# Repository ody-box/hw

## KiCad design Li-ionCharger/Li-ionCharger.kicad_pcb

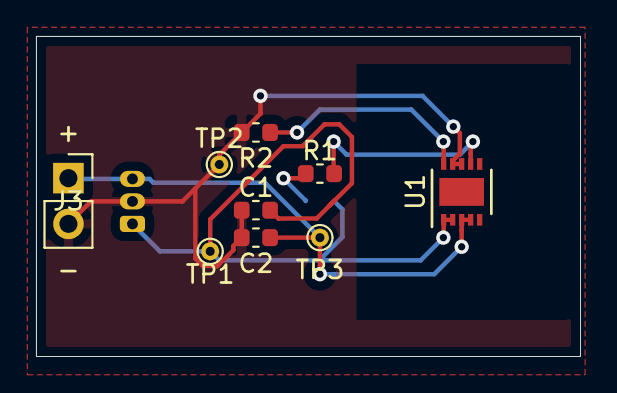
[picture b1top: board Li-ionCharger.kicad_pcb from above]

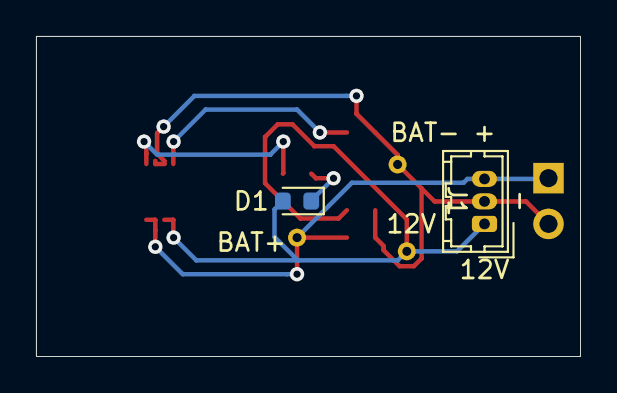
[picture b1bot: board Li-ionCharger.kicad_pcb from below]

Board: 2 copper layers, 30.2 x 17.8 mm, 11 parts (2 on the bottom side), 6 nets.

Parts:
C1, C2: 1uF; C_0603_1608Metric
D1: Blue; LED_0603_1608Metric
J1: Conn_01x03_Male; Hirose_DF13-03P-1.25DSA_1x03_P1.25mm_Vertical
J3: Conn_01x02_Male; PinSocket_1x02_P2.54mm_Vertical
R1: 1k; R_0603_1608Metric
R2: 1.1k 1% E96; R_0603_1608Metric
TP1, TP2, TP3: TestPoint; TestPoint_THTPad_D1.0mm_Drill0.5mm
U1: MCP73213; DFN-10-1EP_3x3mm_P0.5mm_EP1.55x2.48mm

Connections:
12V: C1.1, D1.2, J1.1, TP1.1, U1.1, U1.2
BAT+: C2.1, J1.3, J3.1, TP3.1, U1.3, U1.4
BAT-: C1.2, C2.2, J1.2, J3.2, R2.2, TP2.1, U1.8, U1.9
unnamed: D1.1, R1.2
unnamed: R1.1, U1.7
unnamed: R2.1, U1.10

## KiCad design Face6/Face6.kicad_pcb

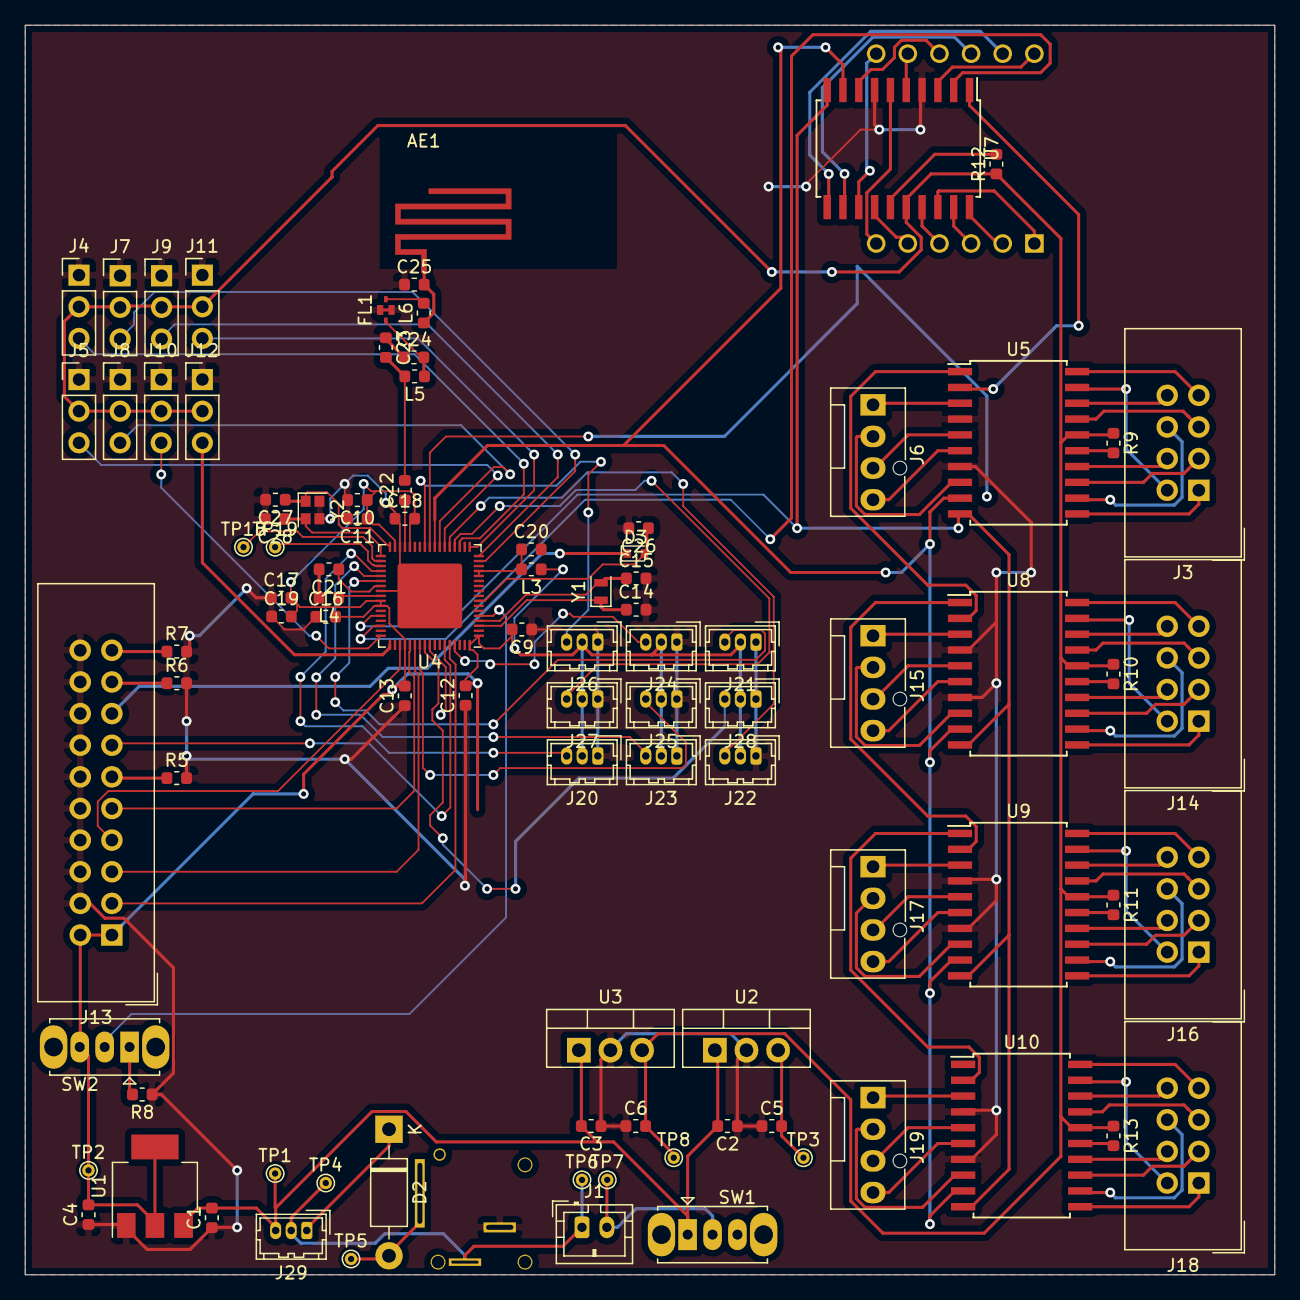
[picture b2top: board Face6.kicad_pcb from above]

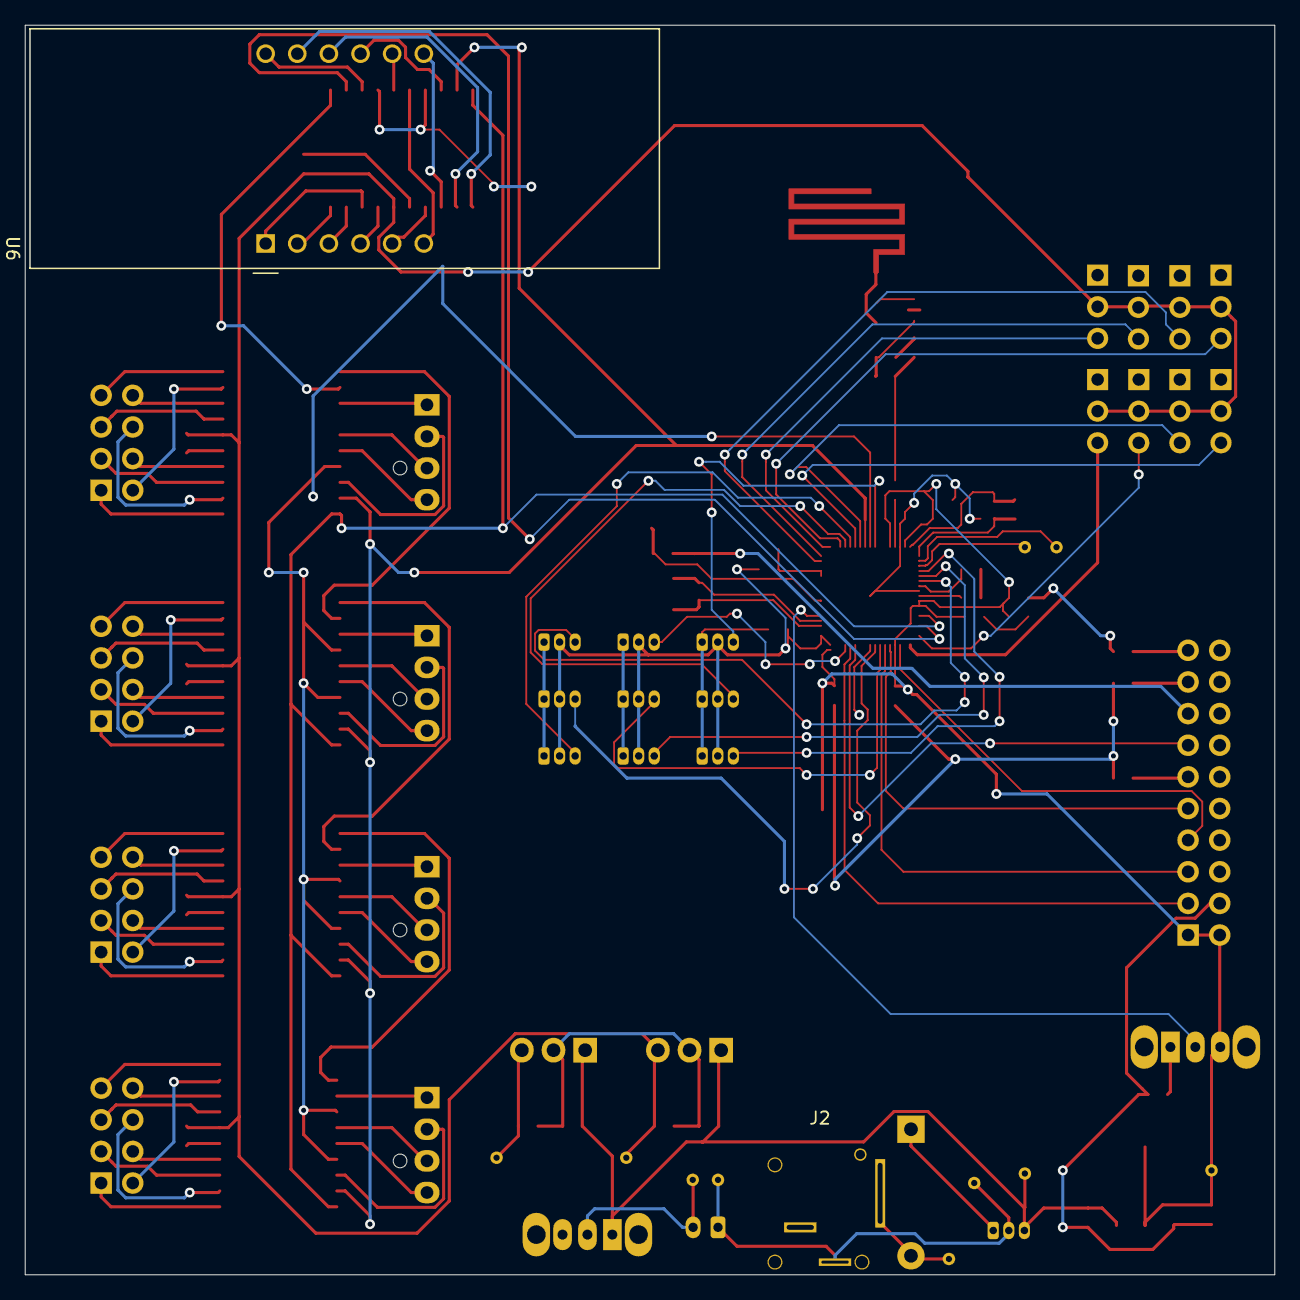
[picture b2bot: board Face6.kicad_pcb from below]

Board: 2 copper layers, 100.3 x 100.3 mm, 96 parts (2 on the bottom side), 125 nets.

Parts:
AE1: Antenna; STM32-Antenna
C1, C5, C6: 0.1uF; C_0603_1608Metric
C2, C3: 0.33uF; C_0603_1608Metric
C4: 10uF; C_0603_1608Metric
C9, C10, C12, C13, C16, C18, C19, C20, C26: 100nF; C_0603_1608Metric
C11: 100pF; C_0603_1608Metric
C14, C15: 10pF; C_0603_1608Metric
C17, C21: 4.7uF; C_0603_1608Metric
C22: 10nF; C_0603_1608Metric
C23: 0.8pF; C_0603_1608Metric
C24: 0.3pF; C_0603_1608Metric
C25: 1.2pF; C_0603_1608Metric
C27, C28: 20pF; C_0603_1608Metric
D2: 1N4007; D_DO-41_SOD81_P10.16mm_Horizontal
D3: BAT54K; D_SOD-523
FL1: DEA162450BT
J1: Conn_01x02_Female; JST_PH_B2B-PH-K_1x02_P2.00mm_Vertical
J2: Barrel_Jack_Switch; KLDVX2020A
J3, J14, J16, J18: Conn_02x04_Odd_Even; IDC-Header_2x04_P2.54mm_Vertical
J4, J5, J7, J8, J9, J10, J11, J12: Conn_01x03_Male; PinHeader_1x03_P2.54mm_Vertical
J6, J15, J17, J19: Conn_01x04; FanPinHeader_1x04_P2.54mm_Vertical
J13: Conn_02x10_Odd_Even; IDC-Header_2x10_P2.54mm_Vertical
J20, J21, J22, J23, J24, J25, J26, J27, J28, J29: Conn_01x03_Male; Hirose_DF13-03P-1.25DSA_1x03_P1.25mm_Vertical
L3: KMZ1608; L_0603_1608Metric
L4: 10uH; L_0603_1608Metric
L5: 2.7nH; L_0603_1608Metric
L6: 3.6nH; R_0603_1608Metric
R5, R6, R7, R8: 10k; R_0603_1608Metric
R9, R10, R11, R13: 22.6k; R_0603_1608Metric
R12: 28k; R_0603_1608Metric
SW1, SW2: SW_SPDT; SW_Slide_1P2T_CK_OS102011MS2Q
TP1, TP2, TP3, TP4, TP5, TP6, TP7, TP8, TP18, TP19: TestPoint; TestPoint_THTPad_D1.0mm_Drill0.5mm
U1: LD1117S33TR_SOT223; SOT-223-3_TabPin2
U2, U3: L7805; TO-220-3_Vertical
U4: STM32WB55REV; QFN-68-1EP_8x8mm_P0.4mm_EP5.2x5.2mm
U5, U7, U8, U9, U10: AS1105WL-T; SOIC-20W_7.5x12.8mm_P1.27mm
U6: CA56-12EWA
Y1: NX2012_32K768; Crystal_SMD_2012-2Pin_2.0x1.2mm
Y2: NX3225SA-32MHz; Crystal_SMD_2016-4Pin_2.0x1.6mm

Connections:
+3V3: C4.2, C9.2, C10.1, C11.1, C12.2, C13.2, C16.2, C17.2, C18.2, C19.2, J13.1, J13.2, J20.2, J21.2, J22.2, J23.2, J24.2, J25.2, J26.2, J27.2, J28.2, L3.1, SW2.3, TP2.1, U1.2, U4.1, U4.30, U4.33, U4.44, U4.45, U4.55, U4.68
+5V: C6.2, J4.2, J5.2, J7.2, J8.2, J9.2, J10.2, J11.2, J12.2, R9.1, R10.1, R11.1, R12.1, R13.1, TP8.1, U3.3, U5.16, U7.16, U8.16, U9.16, U10.16
+5VP: C5.2, TP3.1, U2.3
/Connectors.sch/12V: D2.1, J29.1
/Connectors.sch/BAT+: C1.2, C2.2, C3.2, J29.3, SW1.1, TP1.1, U1.3, U2.1, U3.1
/Connectors.sch/BAT-: J1.1, J2.2, J29.2, TP4.1, TP6.1
/Connectors.sch/DIG0_0: J6.1, U5.3
/Connectors.sch/DIG0_1: J15.1, U8.3
/Connectors.sch/DIG0_2: J17.1, U9.3
/Connectors.sch/DIG0_3: J19.1, U10.3
/Connectors.sch/DIG1_0: J6.2, U5.8
/Connectors.sch/DIG1_1: J15.2, U8.8
/Connectors.sch/DIG1_2: J17.2, U9.8
/Connectors.sch/DIG1_3: J19.2, U10.8
/Connectors.sch/DIG2_0: J6.3, U5.5
/Connectors.sch/DIG2_1: J15.3, U8.5
/Connectors.sch/DIG2_2: J17.3, U9.5
/Connectors.sch/DIG2_3: J19.3, U10.5
/Connectors.sch/DIG3_0: J6.4, U5.6
/Connectors.sch/DIG3_1: J15.4, U8.6
/Connectors.sch/DIG3_2: J17.4, U9.6
/Connectors.sch/DIG3_3: J19.4, U10.6
/Connectors.sch/SEGA_0: J3.1, U5.11
/Connectors.sch/SEGA_1: J14.1, U8.11
/Connectors.sch/SEGA_2: J16.1, U9.11
/Connectors.sch/SEGA_3: J18.1, U10.11
/Connectors.sch/SEGB_0: J3.3, U5.13
/Connectors.sch/SEGB_1: J14.3, U8.13
/Connectors.sch/SEGB_2: J16.3, U9.13
/Connectors.sch/SEGB_3: J18.3, U10.13
/Connectors.sch/SEGC_0: J3.5, U5.17
/Connectors.sch/SEGC_1: J14.5, U8.17
/Connectors.sch/SEGC_2: J16.5, U9.17
/Connectors.sch/SEGC_3: J18.5, U10.17
/Connectors.sch/SEGD_0: J3.7, U5.20
/Connectors.sch/SEGD_1: J14.7, U8.20
/Connectors.sch/SEGD_2: J16.7, U9.20
/Connectors.sch/SEGD_3: J18.7, U10.20
/Connectors.sch/SEGE_0: J3.8, U5.18
/Connectors.sch/SEGE_1: J14.8, U8.18
/Connectors.sch/SEGE_2: J16.8, U9.18
/Connectors.sch/SEGE_3: J18.8, U10.18
/Connectors.sch/SEGF_0: J3.6, U5.12
/Connectors.sch/SEGF_1: J14.6, U8.12
/Connectors.sch/SEGF_2: J16.6, U9.12
/Connectors.sch/SEGF_3: J18.6, U10.12
/Connectors.sch/SEGG_0: J3.4, U5.14
/Connectors.sch/SEGG_1: J14.4, U8.14
/Connectors.sch/SEGG_2: J16.4, U9.14
/Connectors.sch/SEGG_3: J18.4, U10.14
/STM32/GPIO0_2: U4.25, U5.9, U7.9, U8.9, U9.9, U10.9
/STM32/GPIO_EXT0: J20.3, U4.38
/STM32/GPIO_EXT1: J23.3, U4.39
/STM32/GPIO_EXT2: J26.3, U4.27
/STM32/GPIO_EXT4: J21.3, U4.40
/STM32/GPIO_EXT5: J24.3, U4.65
/STM32/GPIO_EXT6: J27.3, U4.21
/STM32/GPIO_EXT7: J22.3, U4.22
/STM32/GPIO_EXT10: J25.3, U4.58
/STM32/GPIO_EXT11: J28.3, U4.59
/STM32/MOSI: U4.49, U7.2
/STM32/PWM1_TM1: J5.3, U4.23
/STM32/PWM1_TM2: J4.3, U4.20
/STM32/PWM2_TM1: J8.3, U4.24
/STM32/PWM2_TM2: J7.3, U4.16
/STM32/PWM3_TM1: J10.3, U4.51
/STM32/PWM3_TM2: J9.3, U4.17
/STM32/PWM4_TM1: J12.3, U4.52
/STM32/PWM4_TM2: J11.3, U4.18
/STM32/SCK: U4.47, U5.10, U7.10, U8.10, U9.10, U10.10
/Sensors/SEGDP_0: J3.2, U5.19
/Sensors/SEGDP_1: J14.2, U8.19
/Sensors/SEGDP_2: J16.2, U9.19
/Sensors/SEGDP_3: J18.2, U10.19
DIG0: U6.12, U7.3
DIG1: U6.9, U7.8
DIG2: U6.8, U7.5
DIG3: U6.6, U7.6
GND: C1.1, C2.1, C3.1, C4.1, C5.1, C6.1, C9.1, C10.2, C11.2, C12.1, C13.1, C14.2, C15.2, C16.1, C17.1, C18.1, C19.1, C20.2, C23.1, C24.1, C25.1, C26.2, C27.2, C28.2, FL1.2, FL1.4, J2.3, J4.1, J5.1, J7.1, J8.1, J9.1, J10.1, J11.1, J12.1, J13.4, J13.6, J13.8, J13.10, J13.12, J13.14, J13.16, J13.18, J13.20, J20.1, J21.1, J22.1, J23.1, J24.1, J25.1, J26.1, J27.1, J28.1, R5.2, R6.2, R7.2, R8.1, U1.1, U2.2, U3.2, U4.32, U4.42, U4.69, U5.4, U5.7, U7.4, U7.7, U8.4, U8.7, U9.4, U9.7, U10.4, U10.7, Y2.3, Y2.4
JTCK: J13.9, U4.56
JTDI: J13.5, U4.57
JTDO: J13.13, U4.63
JTMS: J13.7, U4.54
unnamed: AE1.1, C25.2, L6.1
unnamed: C14.1, U4.3, Y1.1
unnamed: C15.1, U4.4, Y1.2
unnamed: C20.1, L3.2, U4.13, U4.14
unnamed: C21.1, U4.41
unnamed: C21.2, L4.2
unnamed: C22.1, U4.31
unnamed: C22.2, C23.2, L5.2
unnamed: C24.2, FL1.1, L5.1
unnamed: C26.1, D3.2, U4.8
unnamed: C27.1, U4.34, Y2.1
unnamed: C28.1, U4.35, Y2.2
unnamed: D2.2, J2.1, TP5.1
unnamed: FL1.3, L6.2
unnamed: J1.2, SW1.2, TP7.1
unnamed: J13.11, R5.1
unnamed: J13.17, R6.1
unnamed: J13.19, R7.1
unnamed: L4.1, U4.43
unnamed: R8.2, SW2.1
unnamed: R9.2, U5.15
unnamed: R10.2, U8.15
unnamed: R11.2, U9.15
unnamed: R12.2, U7.15
unnamed: R13.2, U10.15
unnamed: SW2.2, U4.5
unnamed: TP18.1, U4.36
unnamed: TP19.1, U4.37
unnamed: U5.1, U8.2
unnamed: U5.2, U7.1
unnamed: U8.1, U9.2
unnamed: U9.1, U10.2
SEGA: U6.11, U7.11
SEGB: U6.7, U7.13
SEGC: U6.4, U7.17
SEGD: U6.2, U7.20
SEGDP: U6.3, U7.19
SEGE: U6.1, U7.18
SEGF: U6.10, U7.12
SEGG: U6.5, U7.14
nJTRST: J13.3, U4.64
nSRST: D3.1, J13.15

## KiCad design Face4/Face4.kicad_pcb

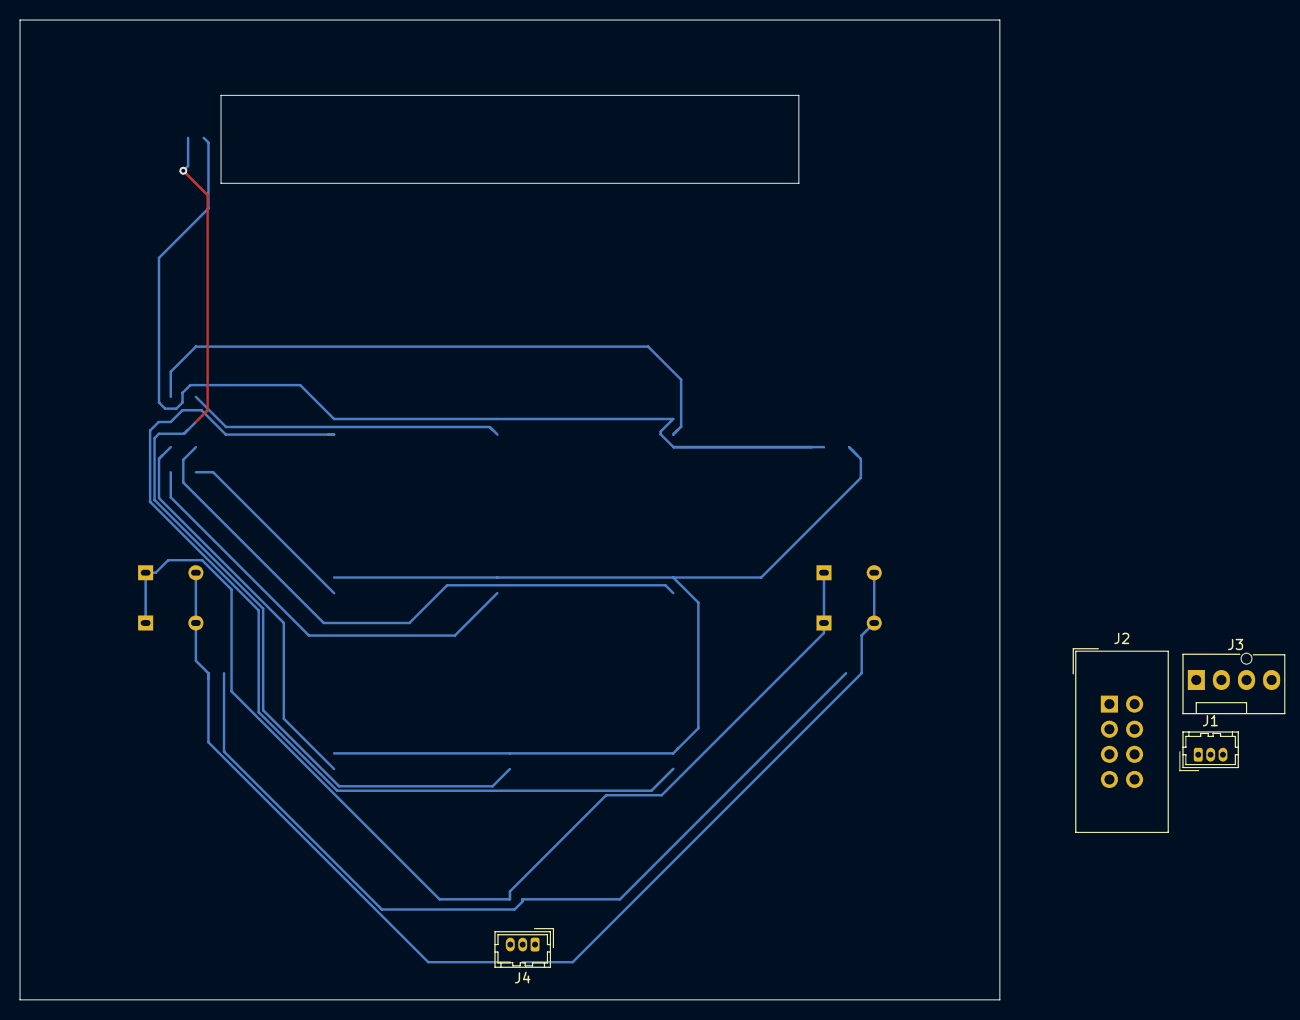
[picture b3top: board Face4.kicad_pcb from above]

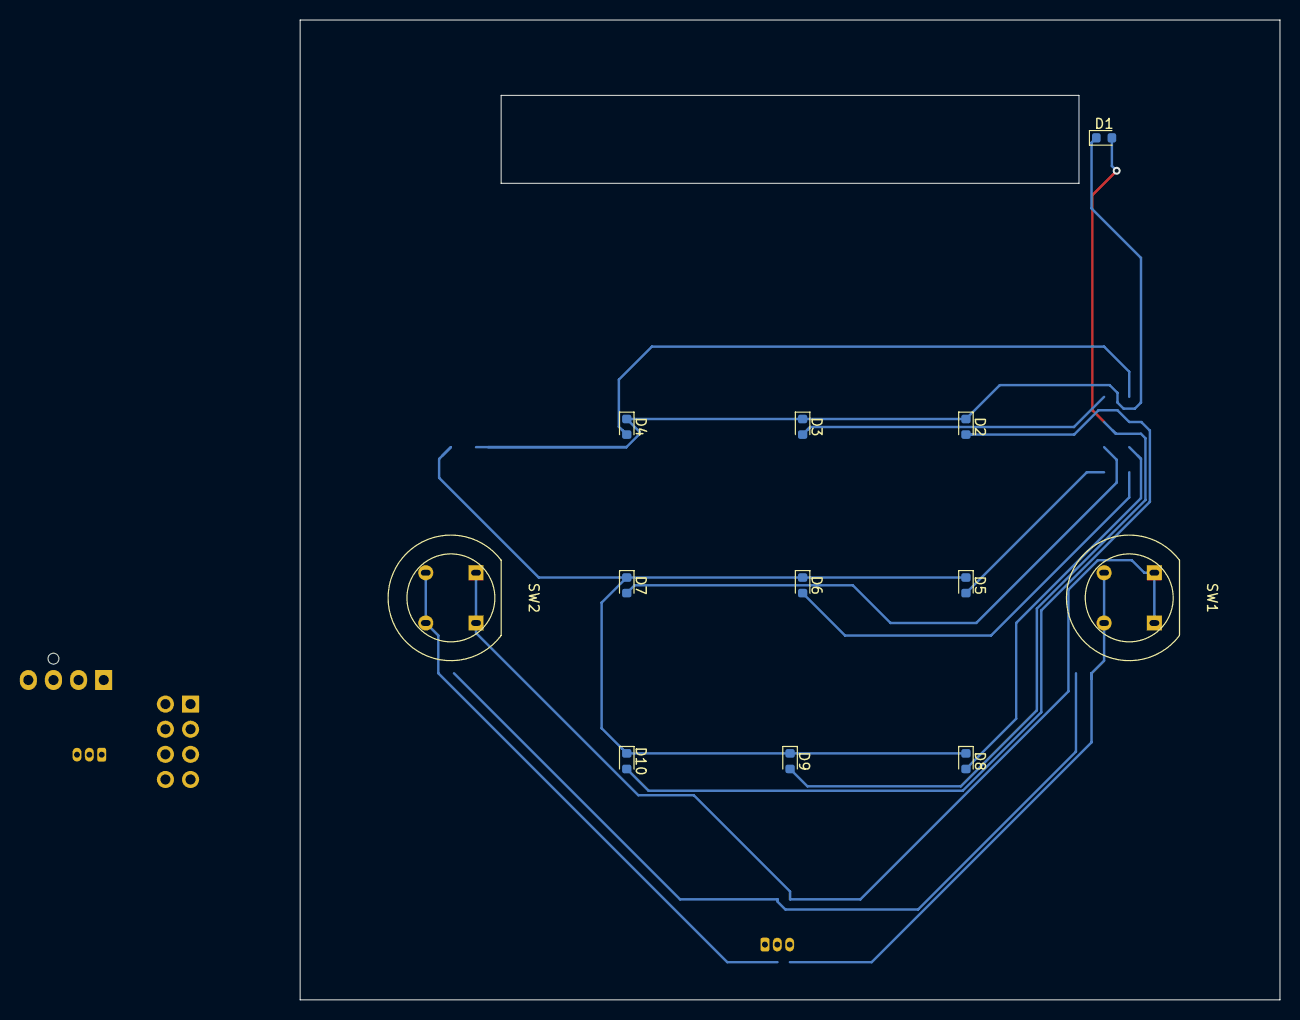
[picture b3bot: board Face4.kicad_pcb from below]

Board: 2 copper layers, 99.1 x 99.1 mm, 16 parts (12 on the bottom side), 14 nets.

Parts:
D1, D2, D3, D4, D5, D6, D7, D8, D9, D10: LED; LED_0603_1608Metric
J1, J4: Conn_01x03_Male; Hirose_DF13-03P-1.25DSA_1x03_P1.25mm_Vertical
J2: Conn_02x04_Odd_Even; IDC-Header_2x04_P2.54mm_Vertical
J3: Conn_01x04_Male; FanPinHeader_1x04_P2.54mm_Vertical
SW1, SW2: SW_Push; D6_Switch

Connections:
3.3V: J1.2, J4.2
DIG0: D1.1, D2.1, J3.1
DIG1: D3.1, D4.1, D5.1, D6.1, D7.1, D8.1, D9.1, D10.1, J3.2
GND: J1.1, J4.1, SW1.1, SW2.1
GPIO0: J1.3, SW2.2
GPIO1: J4.3, SW1.2
SEGA: D1.2, D3.2, J2.1
SEGB: D2.2, D4.2, J2.3
SEGC: D5.2, J2.5
SEGD: D6.2, J2.7
SEGDP: D10.2, J2.2
SEGE: D7.2, J2.8
SEGF: D8.2, J2.6
SEGG: D9.2, J2.4

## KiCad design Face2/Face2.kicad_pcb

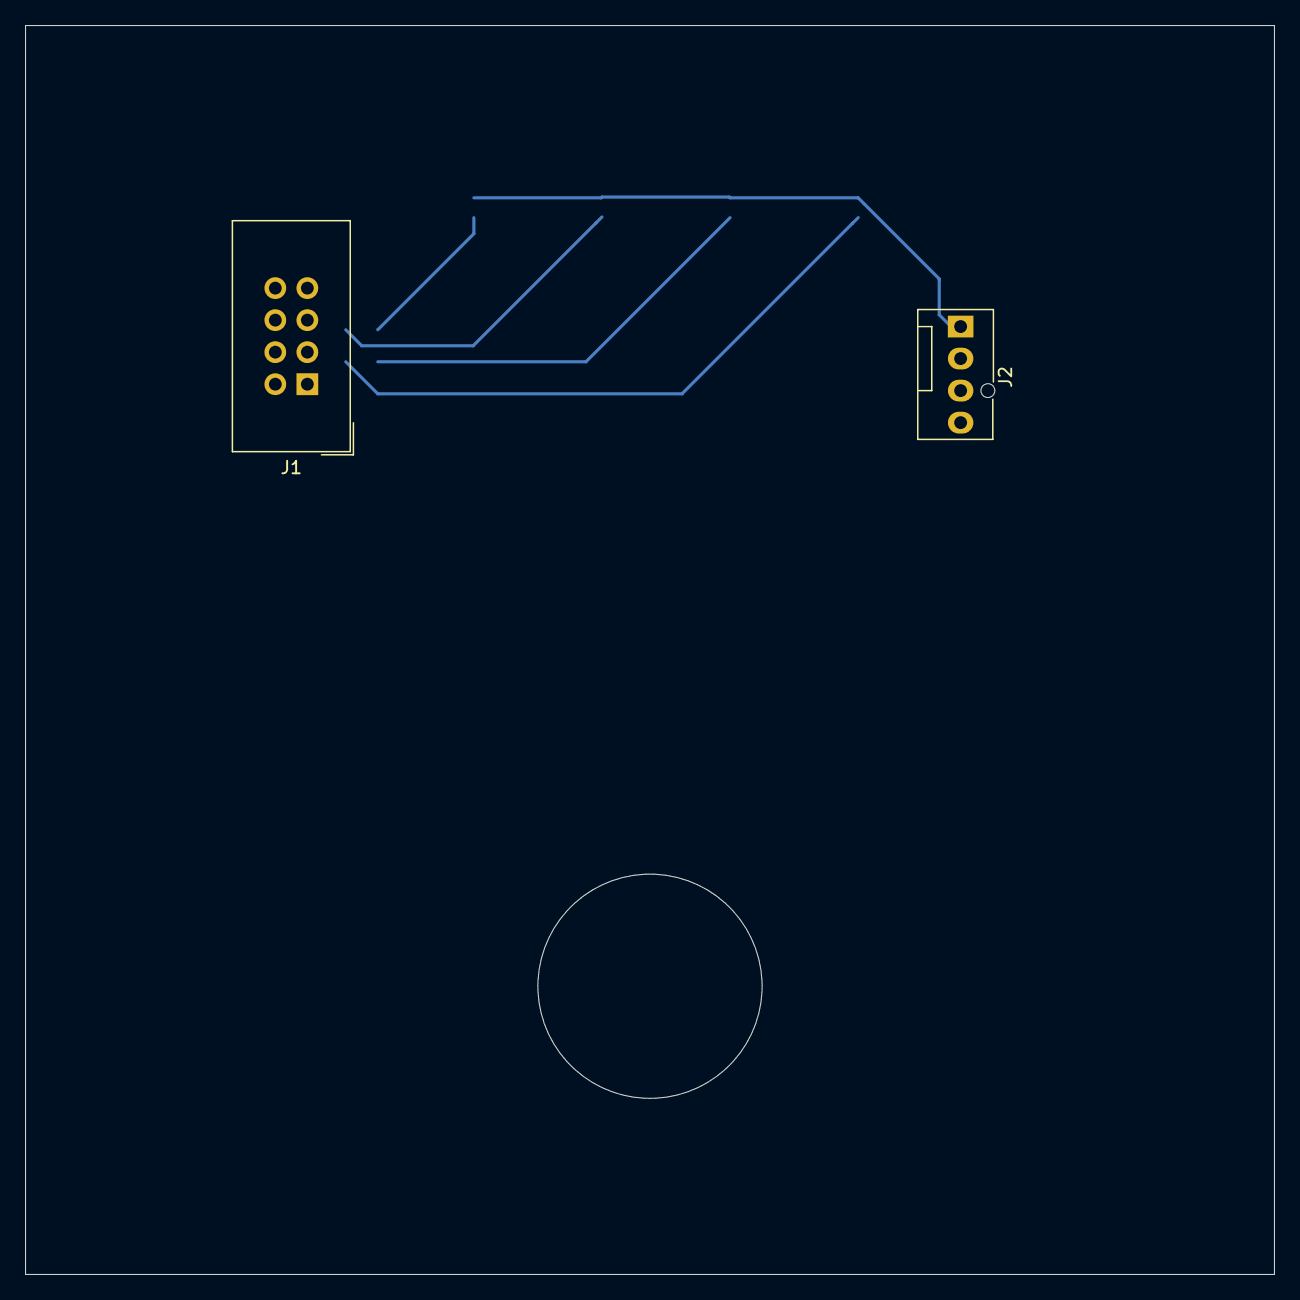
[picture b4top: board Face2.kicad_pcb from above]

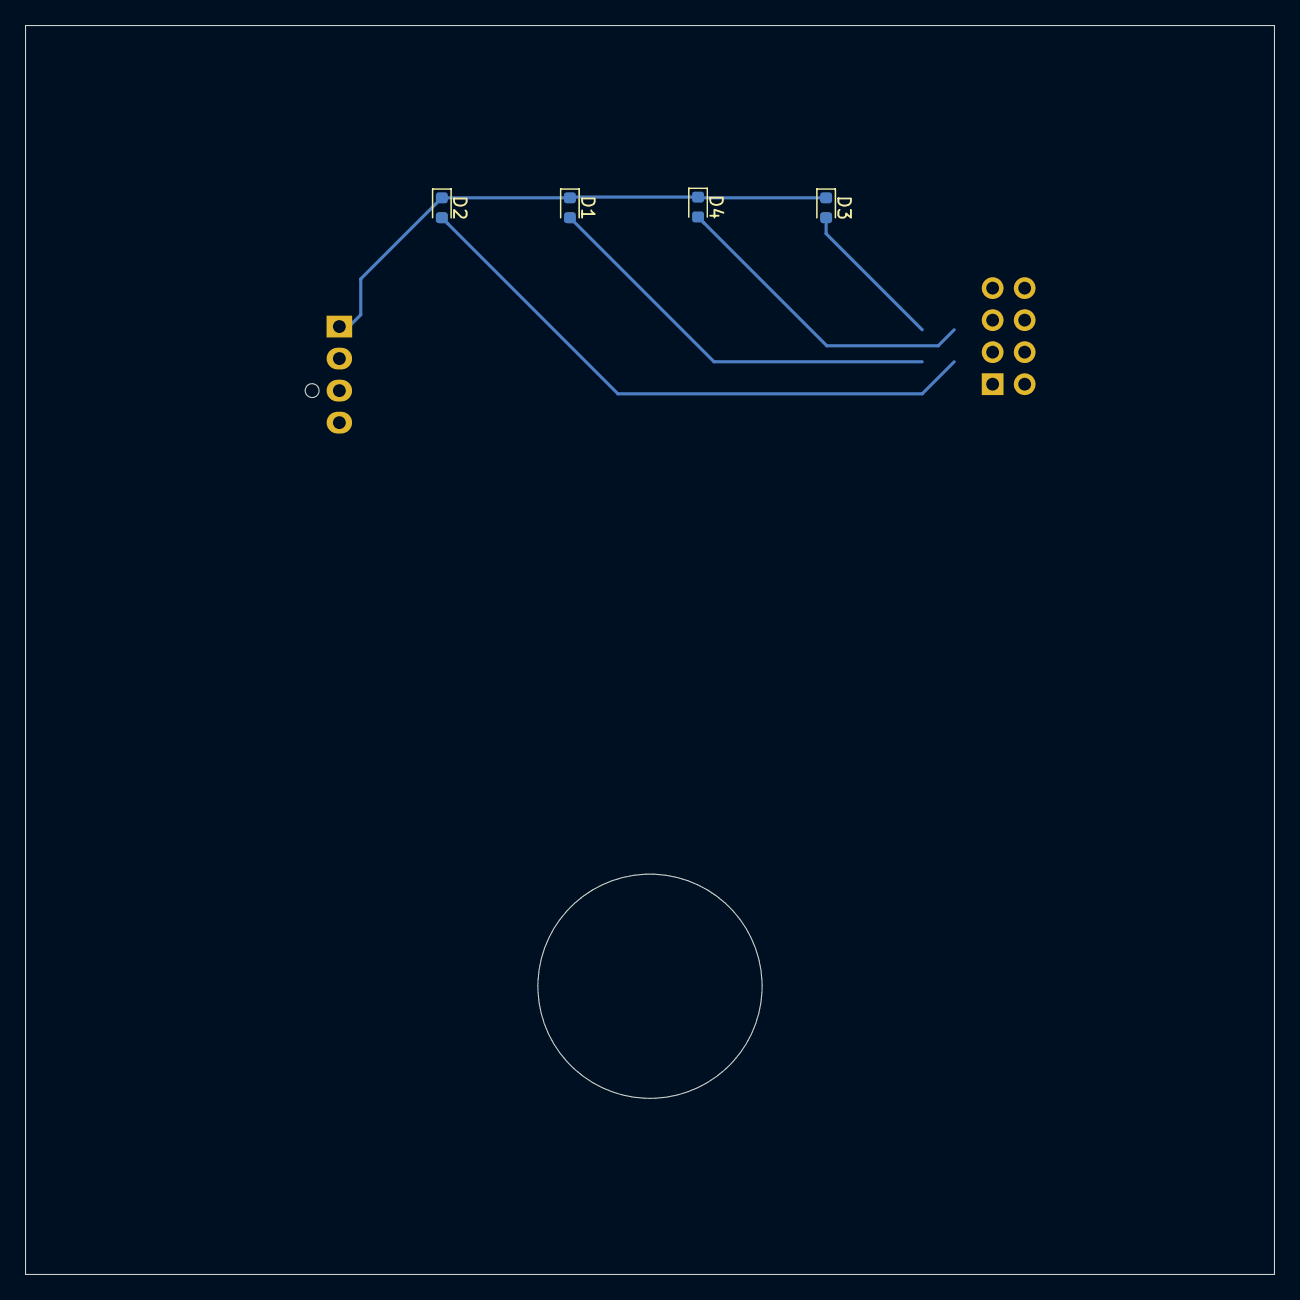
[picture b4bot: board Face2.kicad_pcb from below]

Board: 2 copper layers, 99.1 x 99.1 mm, 6 parts (4 on the bottom side), 5 nets.

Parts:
D1, D2, D3, D4: LED; LED_0603_1608Metric
J1: Conn_02x04_Odd_Even; IDC-Header_2x04_P2.54mm_Vertical
J2: Conn_01x04_Male; FanPinHeader_1x04_P2.54mm_Vertical

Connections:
DIG0: D1.1, D2.1, D3.1, D4.1, J2.1
SEGA: D1.2, J1.1
SEGB: D2.2, J1.3
SEGC: D3.2, J1.5
SEGD: D4.2, J1.7

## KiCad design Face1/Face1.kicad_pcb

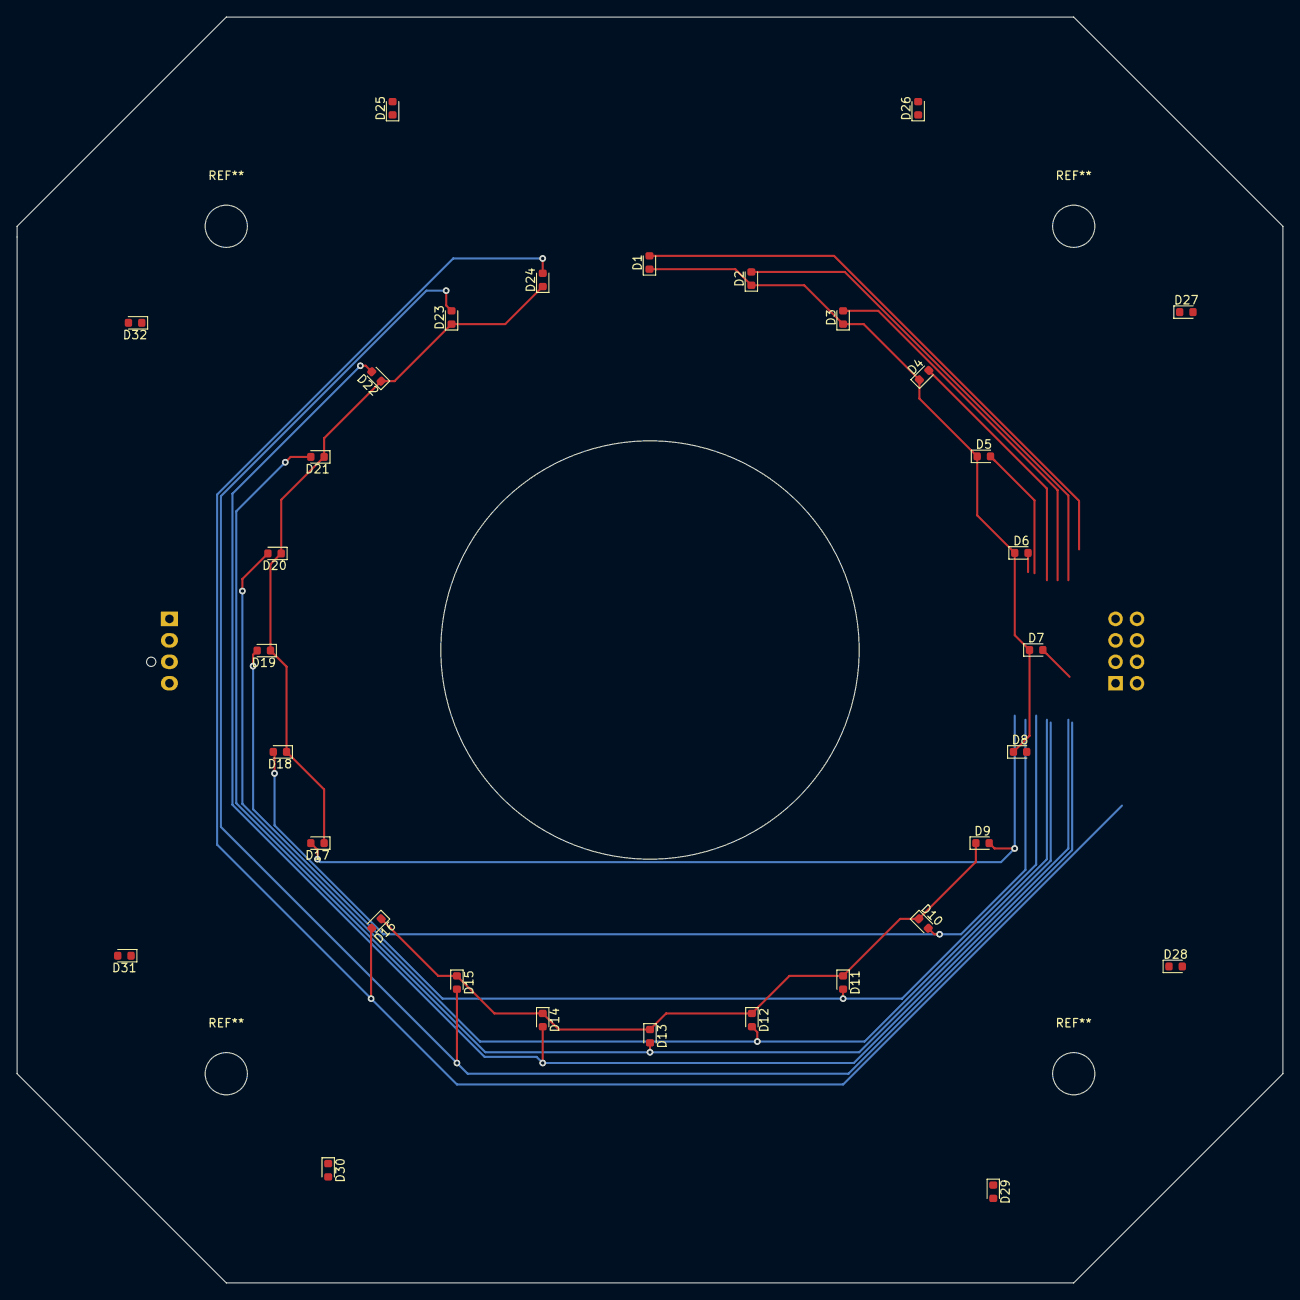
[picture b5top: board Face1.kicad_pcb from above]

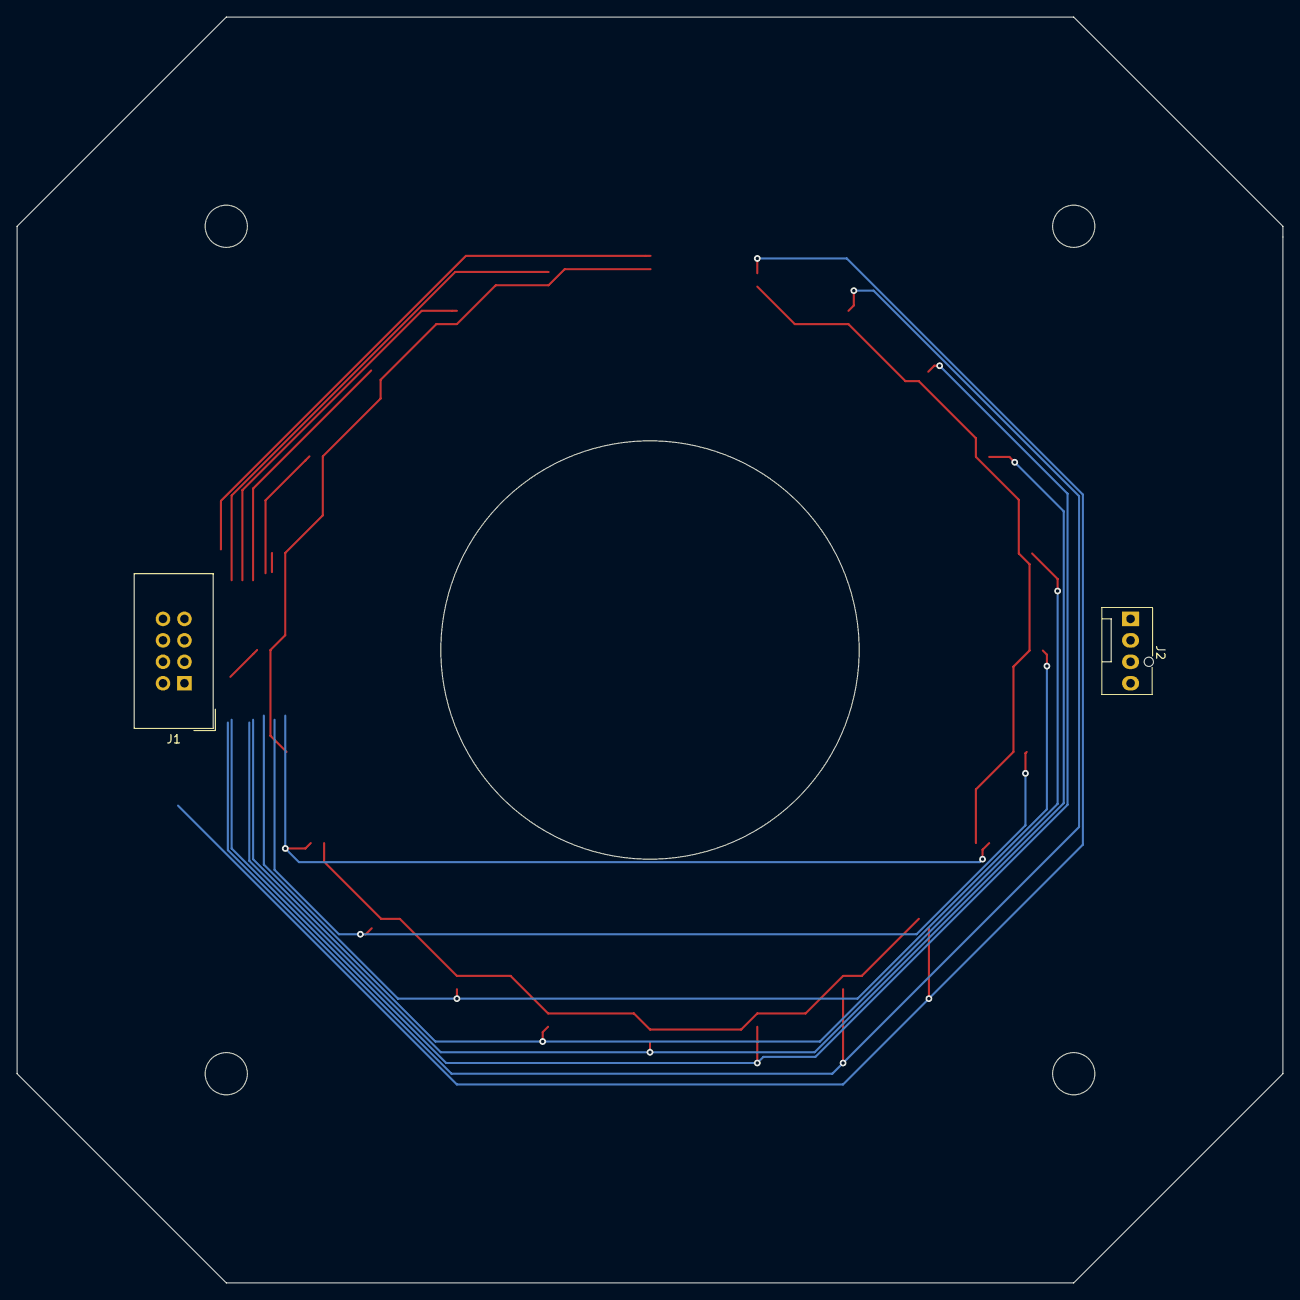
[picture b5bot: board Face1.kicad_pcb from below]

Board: 2 copper layers, 149.9 x 149.9 mm, 34 parts (2 on the bottom side), 12 nets.

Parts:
D1, D2, D3, D4, D5, D6, D7, D8, D9, D10, D11, D12, D13, D14, D15, D16, D17, D18, D19, D20, D21, D22, D23, D24, D25, D26, D27, D28, D29, D30, D31, D32: LED; LED_0603_1608Metric
J1: Conn_02x04_Odd_Even; IDC-Header_2x04_P2.54mm_Vertical
J2: Conn_01x04_Male; FanPinHeader_1x04_P2.54mm_Vertical

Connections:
DIG0: D1.1, D2.1, D3.1, D4.1, D5.1, D6.1, D7.1, D8.1, J2.1
DIG1: D9.1, D10.1, D11.1, D12.1, D13.1, D14.1, D15.1, D16.1, J2.2
DIG2: D17.1, D18.1, D19.1, D20.1, D21.1, D22.1, D23.1, D24.1, J2.3
DIG3: D25.1, D26.1, D27.1, D28.1, D29.1, D30.1, D31.1, D32.1, J2.4
SEGA: D1.2, D9.2, D17.2, D25.2, J1.1
SEGB: D2.2, D10.2, D18.2, D26.2, J1.3
SEGC: D3.2, D11.2, D19.2, D27.2, J1.5
SEGD: D4.2, D12.2, D20.2, D28.2, J1.7
SEGDP: D8.2, D16.2, D24.2, D32.2, J1.2
SEGE: D5.2, D13.2, D21.2, D29.2, J1.8
SEGF: D6.2, D14.2, D22.2, D30.2, J1.6
SEGG: D7.2, D15.2, D23.2, D31.2, J1.4
